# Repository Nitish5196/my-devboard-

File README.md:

# RP2040 Development Board
I made my very own Dev board using RP2040, i followed this guide :https://stasis.hackclub.com/starter-projects/devboard
You can find the PCB schematic, Gerber files, BOM, and CPL in the repository files above.
This is wht the Dev Board looks like :

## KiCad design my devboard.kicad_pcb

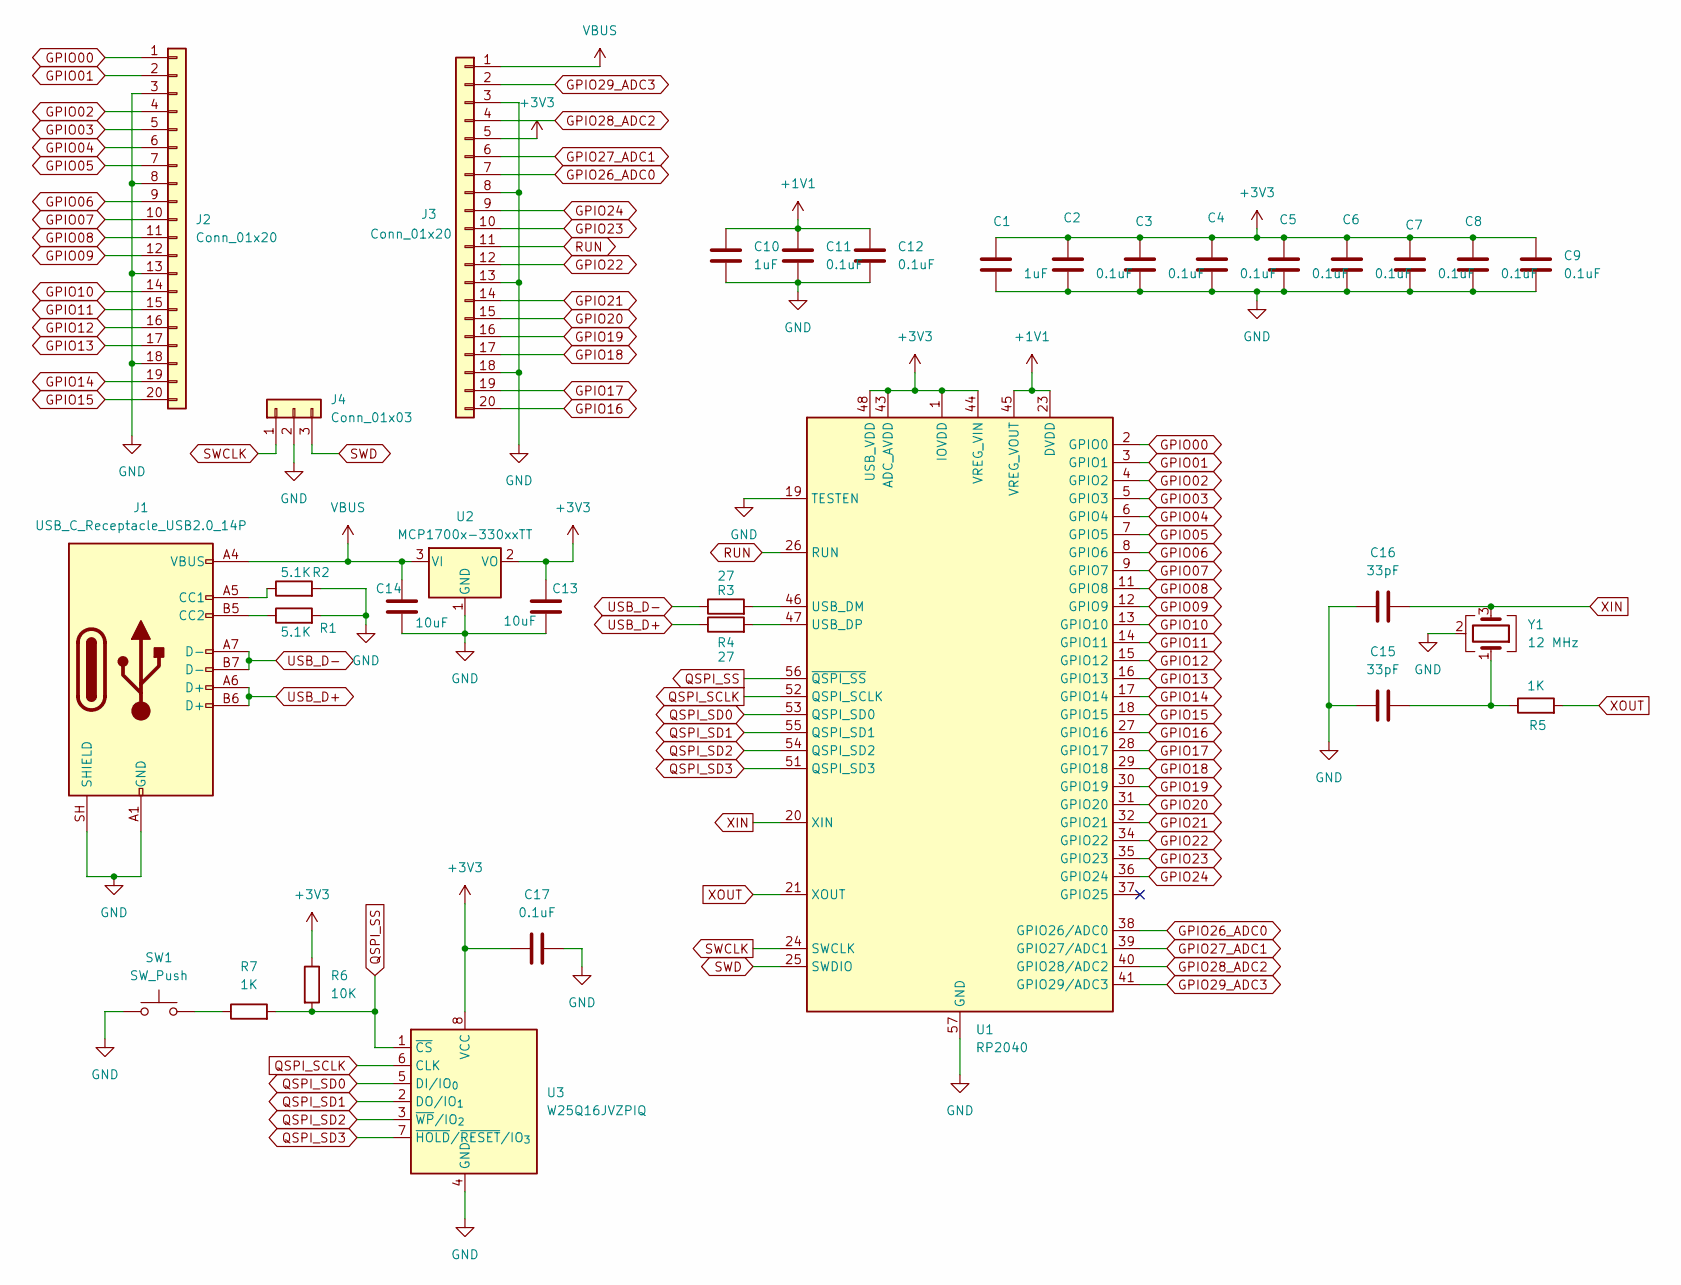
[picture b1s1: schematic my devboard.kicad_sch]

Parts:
C1, C10: 1uF; C_0402_1005Metric
C2, C3, C4, C5, C6, C7, C8, C9, C11, C12, C17: 0.1uF; C_0402_1005Metric
C13, C14: 10uF; C_0603_1608Metric
C15, C16: 33pF; C_0603_1608Metric
J1: USB_C_Receptacle_USB2.0_14P; USB_C_Receptacle_HRO_TYPE-C-31-M-12
J2, J3: Conn_01x20; PinHeader_1x20_P2.54mm_Vertical
J4: Conn_01x03; PinHeader_1x03_P2.54mm_Vertical
R1, R2: 5.1K; R_0402_1005Metric
R3, R4: 27; R_0402_1005Metric
R5, R7: 1K; R_0402_1005Metric
R6: 10K; R_0402_1005Metric
SW1: SW_Push; SW_Push_SPST_NO_Alps_SKRK
U1: RP2040; QFN-56-1EP_7x7mm_P0.4mm_EP3.2x3.2mm
U2: MCP1700x-330xxTT; SOT-23
U3: W25Q16JVZPIQ; Winbond_USON-8-1EP_3x2mm_P0.5mm_EP0.2x1.6mm
Y1: 12 MHz; Crystal_SMD_3225-4Pin_3.2x2.5mm

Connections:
+1V1: C10.1, C11.1, C12.1, U1.23 (DVDD), U1.45 (VREG_VOUT), U1.50 (DVDD)
+3V3: C1.1, C2.1, C3.1, C4.1, C5.1, C6.1, C7.1, C8.1, C9.1, C13.1, C17.1, J3.5, R6.1, U1.1 (IOVDD), U1.10 (IOVDD), U1.22 (IOVDD), U1.33 (IOVDD), U1.42 (IOVDD), U1.43 (ADC_AVDD), U1.44 (VREG_VIN), U1.48 (USB_VDD), U1.49 (IOVDD), U2.2 (VO), U3.8 (VCC)
GND: C1.2, C2.2, C3.2, C4.2, C5.2, C6.2, C7.2, C8.2, C9.2, C10.2, C11.2, C12.2, C13.2, C14.2, C15.1, C16.1, C17.2, J1.A1 (GND), J1.A12 (GND), J1.B1 (GND), J1.B12 (GND), J1.SH (SHIELD), J2.3, J2.8, J2.13, J2.18, J3.3, J3.8, J3.13, J3.18, J4.2, R1.2, R2.2, SW1.1, U1.19 (TESTEN), U1.57 (GND), U2.1 (GND), U3.4 (GND), Y1.2 (G), Y1.4 (G)
GPIO00: J2.1, U1.2 (GPIO0)
GPIO01: J2.2, U1.3 (GPIO1)
GPIO02: J2.4, U1.4 (GPIO2)
GPIO03: J2.5, U1.5 (GPIO3)
GPIO04: J2.6, U1.6 (GPIO4)
GPIO05: J2.7, U1.7 (GPIO5)
GPIO06: J2.9, U1.8 (GPIO6)
GPIO07: J2.10, U1.9 (GPIO7)
GPIO08: J2.11, U1.11 (GPIO8)
GPIO09: J2.12, U1.12 (GPIO9)
GPIO10: J2.14, U1.13 (GPIO10)
GPIO11: J2.15, U1.14 (GPIO11)
GPIO12: J2.16, U1.15 (GPIO12)
GPIO13: J2.17, U1.16 (GPIO13)
GPIO14: J2.19, U1.17 (GPIO14)
GPIO15: J2.20, U1.18 (GPIO15)
GPIO16: J3.20, U1.27 (GPIO16)
GPIO17: J3.19, U1.28 (GPIO17)
GPIO18: J3.17, U1.29 (GPIO18)
GPIO19: J3.16, U1.30 (GPIO19)
GPIO20: J3.15, U1.31 (GPIO20)
GPIO21: J3.14, U1.32 (GPIO21)
GPIO22: J3.12, U1.34 (GPIO22)
GPIO23: J3.10, U1.35 (GPIO23)
GPIO24: J3.9, U1.36 (GPIO24)
GPIO26_ADC0: J3.7, U1.38 (GPIO26/ADC0)
GPIO27_ADC1: J3.6, U1.39 (GPIO27/ADC1)
GPIO28_ADC2: J3.4, U1.40 (GPIO28/ADC2)
GPIO29_ADC3: J3.2, U1.41 (GPIO29/ADC3)
unnamed: C15.2, R5.1, Y1.1
unnamed: J1.A5 (CC1), R2.1
unnamed: J1.B5 (CC2), R1.1
unnamed: R7.1, SW1.2
unnamed: R3.2, U1.46 (USB_DM)
unnamed: R4.2, U1.47 (USB_DP)
QSPI_SCLK: U1.52 (QSPI_SCLK), U3.6 (CLK)
QSPI_SD0: U1.53 (QSPI_SD0), U3.5 (DI/IO_{0})
QSPI_SD1: U1.55 (QSPI_SD1), U3.2 (DO/IO_{1})
QSPI_SD2: U1.54 (QSPI_SD2), U3.3 (~WP/IO_{2})
QSPI_SD3: U1.51 (QSPI_SD3), U3.7 (~HOLD/~RESET/IO_{3})
QSPI_SS: R6.2, R7.2, U1.56 (~QSPI_SS), U3.1 (~CS)
RUN: J3.11, U1.26 (RUN)
SWCLK: J4.1, U1.24 (SWCLK)
SWD: J4.3, U1.25 (SWDIO)
USB_D+: J1.A6 (D+), J1.B6 (D+), R4.1
USB_D-: J1.A7 (D-), J1.B7 (D-), R3.1
VBUS: C14.1, J1.A4 (VBUS), J1.A9 (VBUS), J1.B4 (VBUS), J1.B9 (VBUS), J3.1, U2.3 (VI)
XIN: C16.2, U1.20 (XIN), Y1.3
XOUT: R5.2, U1.21 (XOUT)

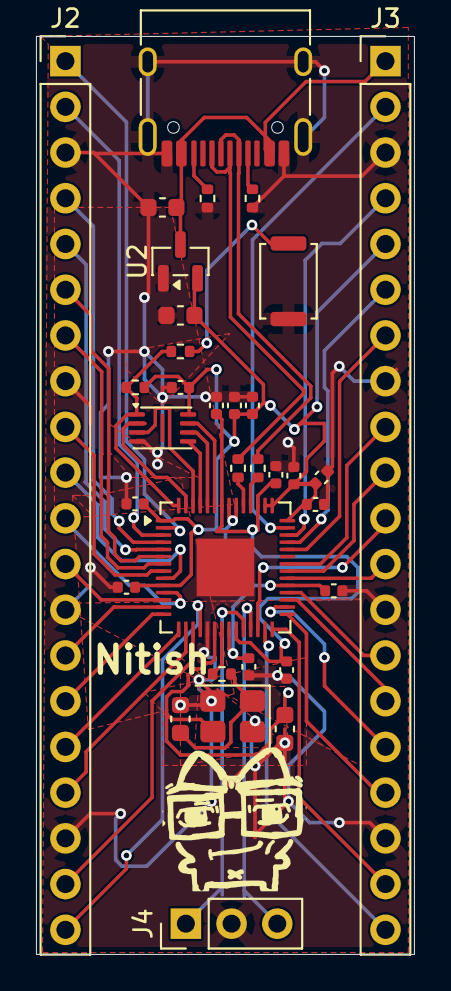
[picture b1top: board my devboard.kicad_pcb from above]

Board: 2 copper layers, 21.0 x 51.0 mm, 33 parts (0 on the bottom side), 52 nets.

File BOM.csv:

"Id";"Designator";"Footprint";"Quantity";"Designation";"Supplier and ref";
1;"C1, C10";"C_0402_1005Metric";2;"1uF";;;
2;"C2, C3, C4, C5, C6, C7, C8, C9, C11, C12, C17";"C_0402_1005Metric";11;"0.1uF";;;
3;"C13, C14";"C_0603_1608Metric";2;"10uF";;;
4;"C15, C16";"C_0603_1608Metric";2;"33pF";;;
5;"J1";"USB_C_Receptacle_HRO_TYPE-C-31-M-12";1;"USB_C_Receptacle_USB2.0_14P";;;
6;"J2, J3";"PinHeader_1x20_P2.54mm_Vertical";2;"Conn_01x20";;;
7;"J4";"PinHeader_1x03_P2.54mm_Vertical";1;"Conn_01x03";;;
8;"R1, R2";"R_0402_1005Metric";2;"5.1K";;;
9;"R3, R4";"R_0402_1005Metric";2;"27";;;
10;"R5, R7";"R_0402_1005Metric";2;"1K";;;
11;"R6";"R_0402_1005Metric";1;"10K";;;
12;"SW1";"SW_Push_SPST_NO_Alps_SKRK";1;"SW_Push";;;
13;"U1";"QFN-56-1EP_7x7mm_P0.4mm_EP3.2x3.2mm";1;"RP2040";;;
14;"U2";"SOT-23";1;"MCP1700x-330xxTT";;;
15;"U3";"Winbond_USON-8-1EP_3x2mm_P0.5mm_EP0.2x1.6mm";1;"W25Q16JVZPIQ";;;
16;"Y1";"Crystal_SMD_3225-4Pin_3.2x2.5mm";1;"12 MHz";;;
